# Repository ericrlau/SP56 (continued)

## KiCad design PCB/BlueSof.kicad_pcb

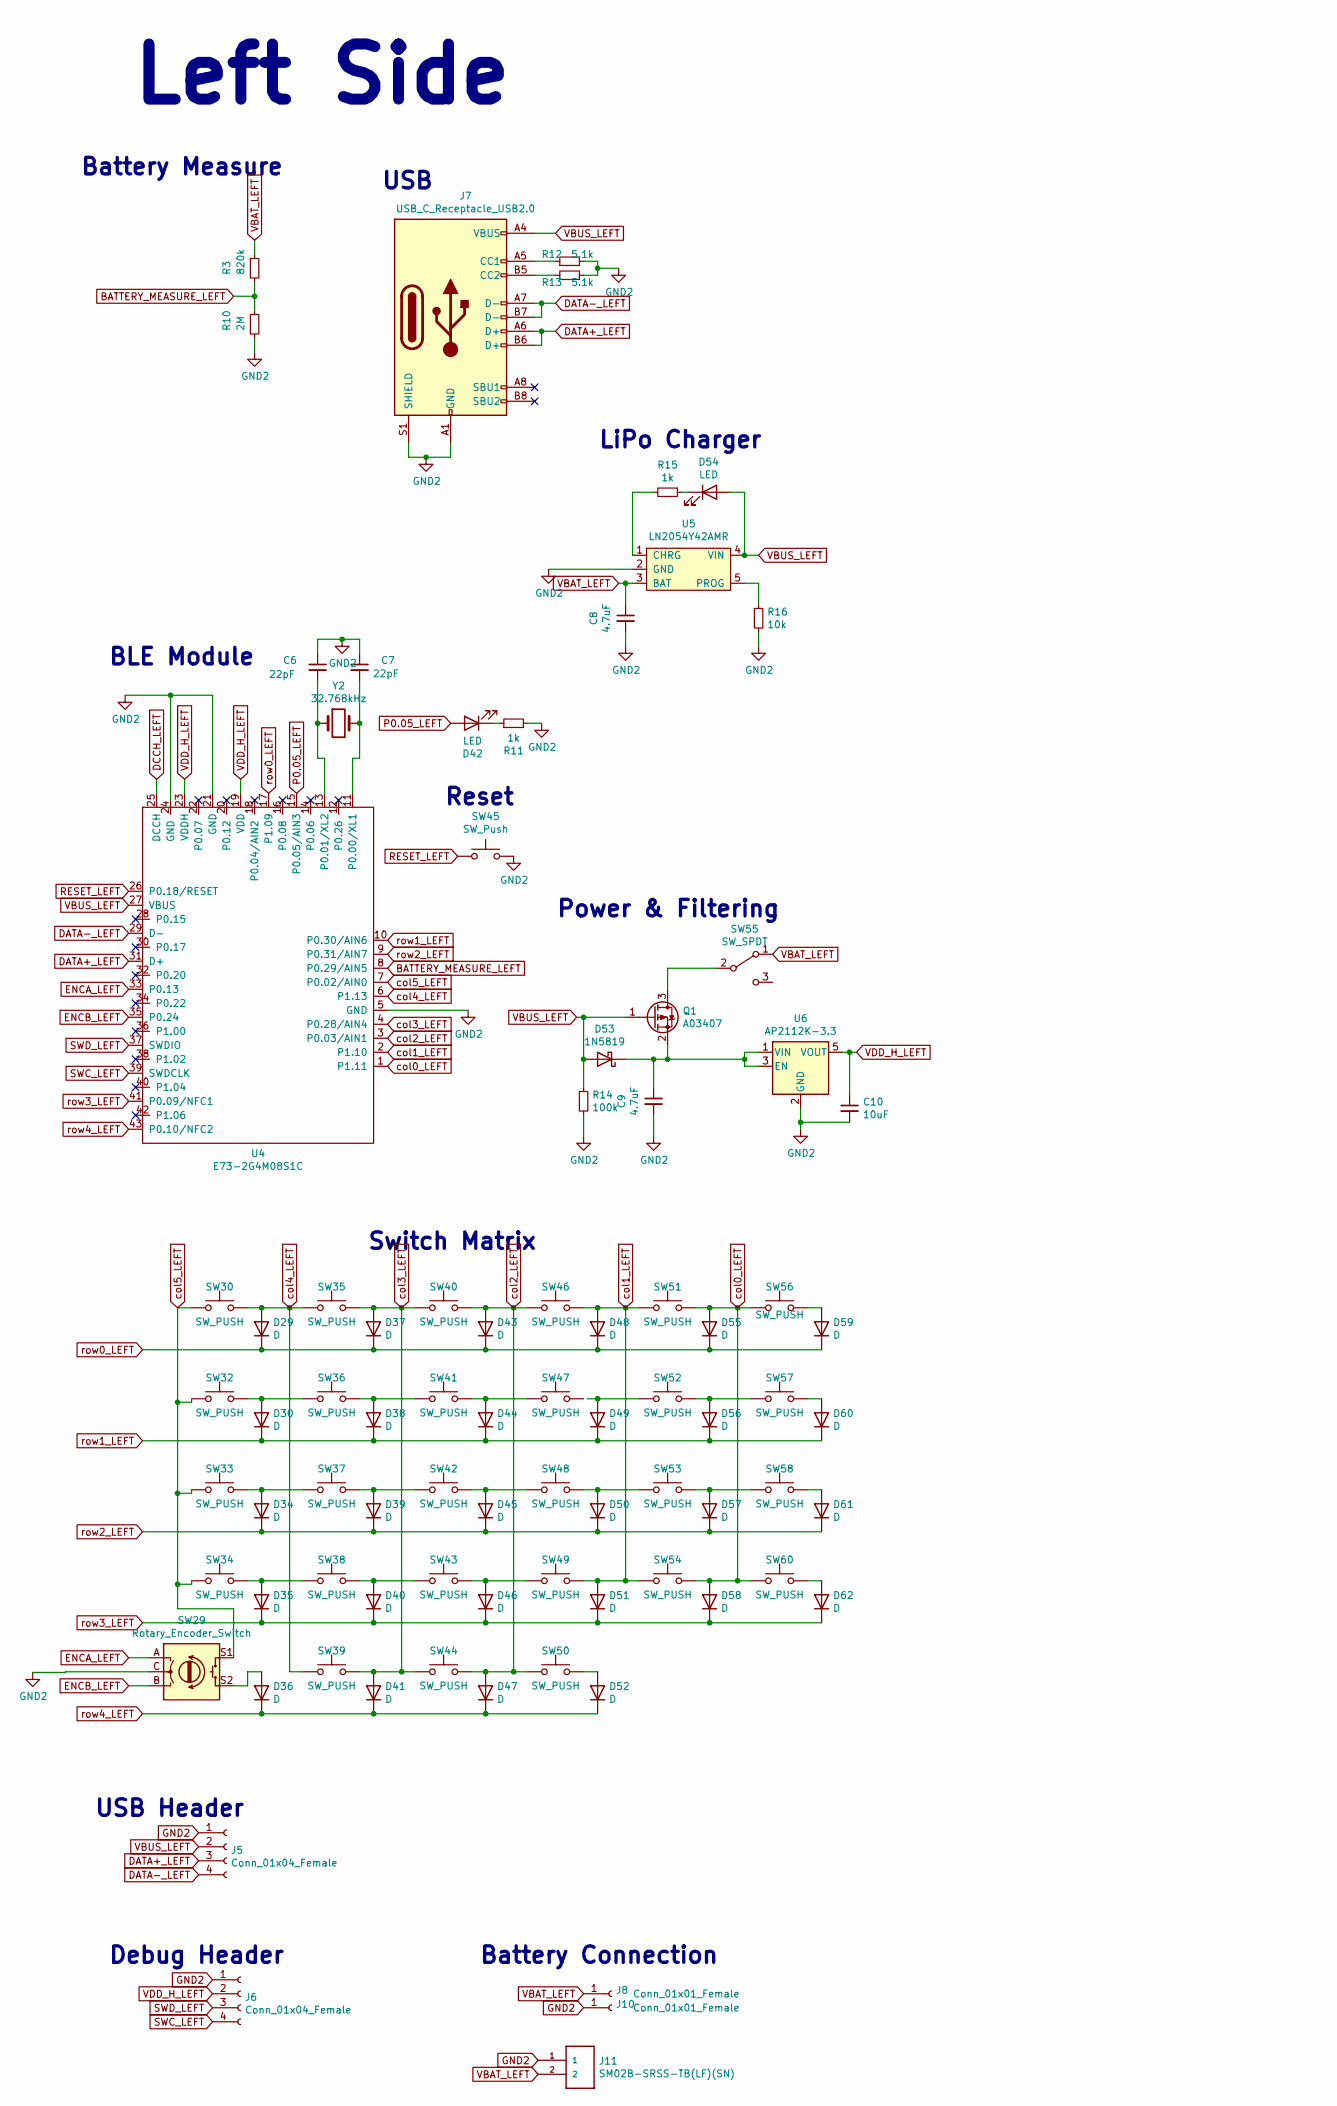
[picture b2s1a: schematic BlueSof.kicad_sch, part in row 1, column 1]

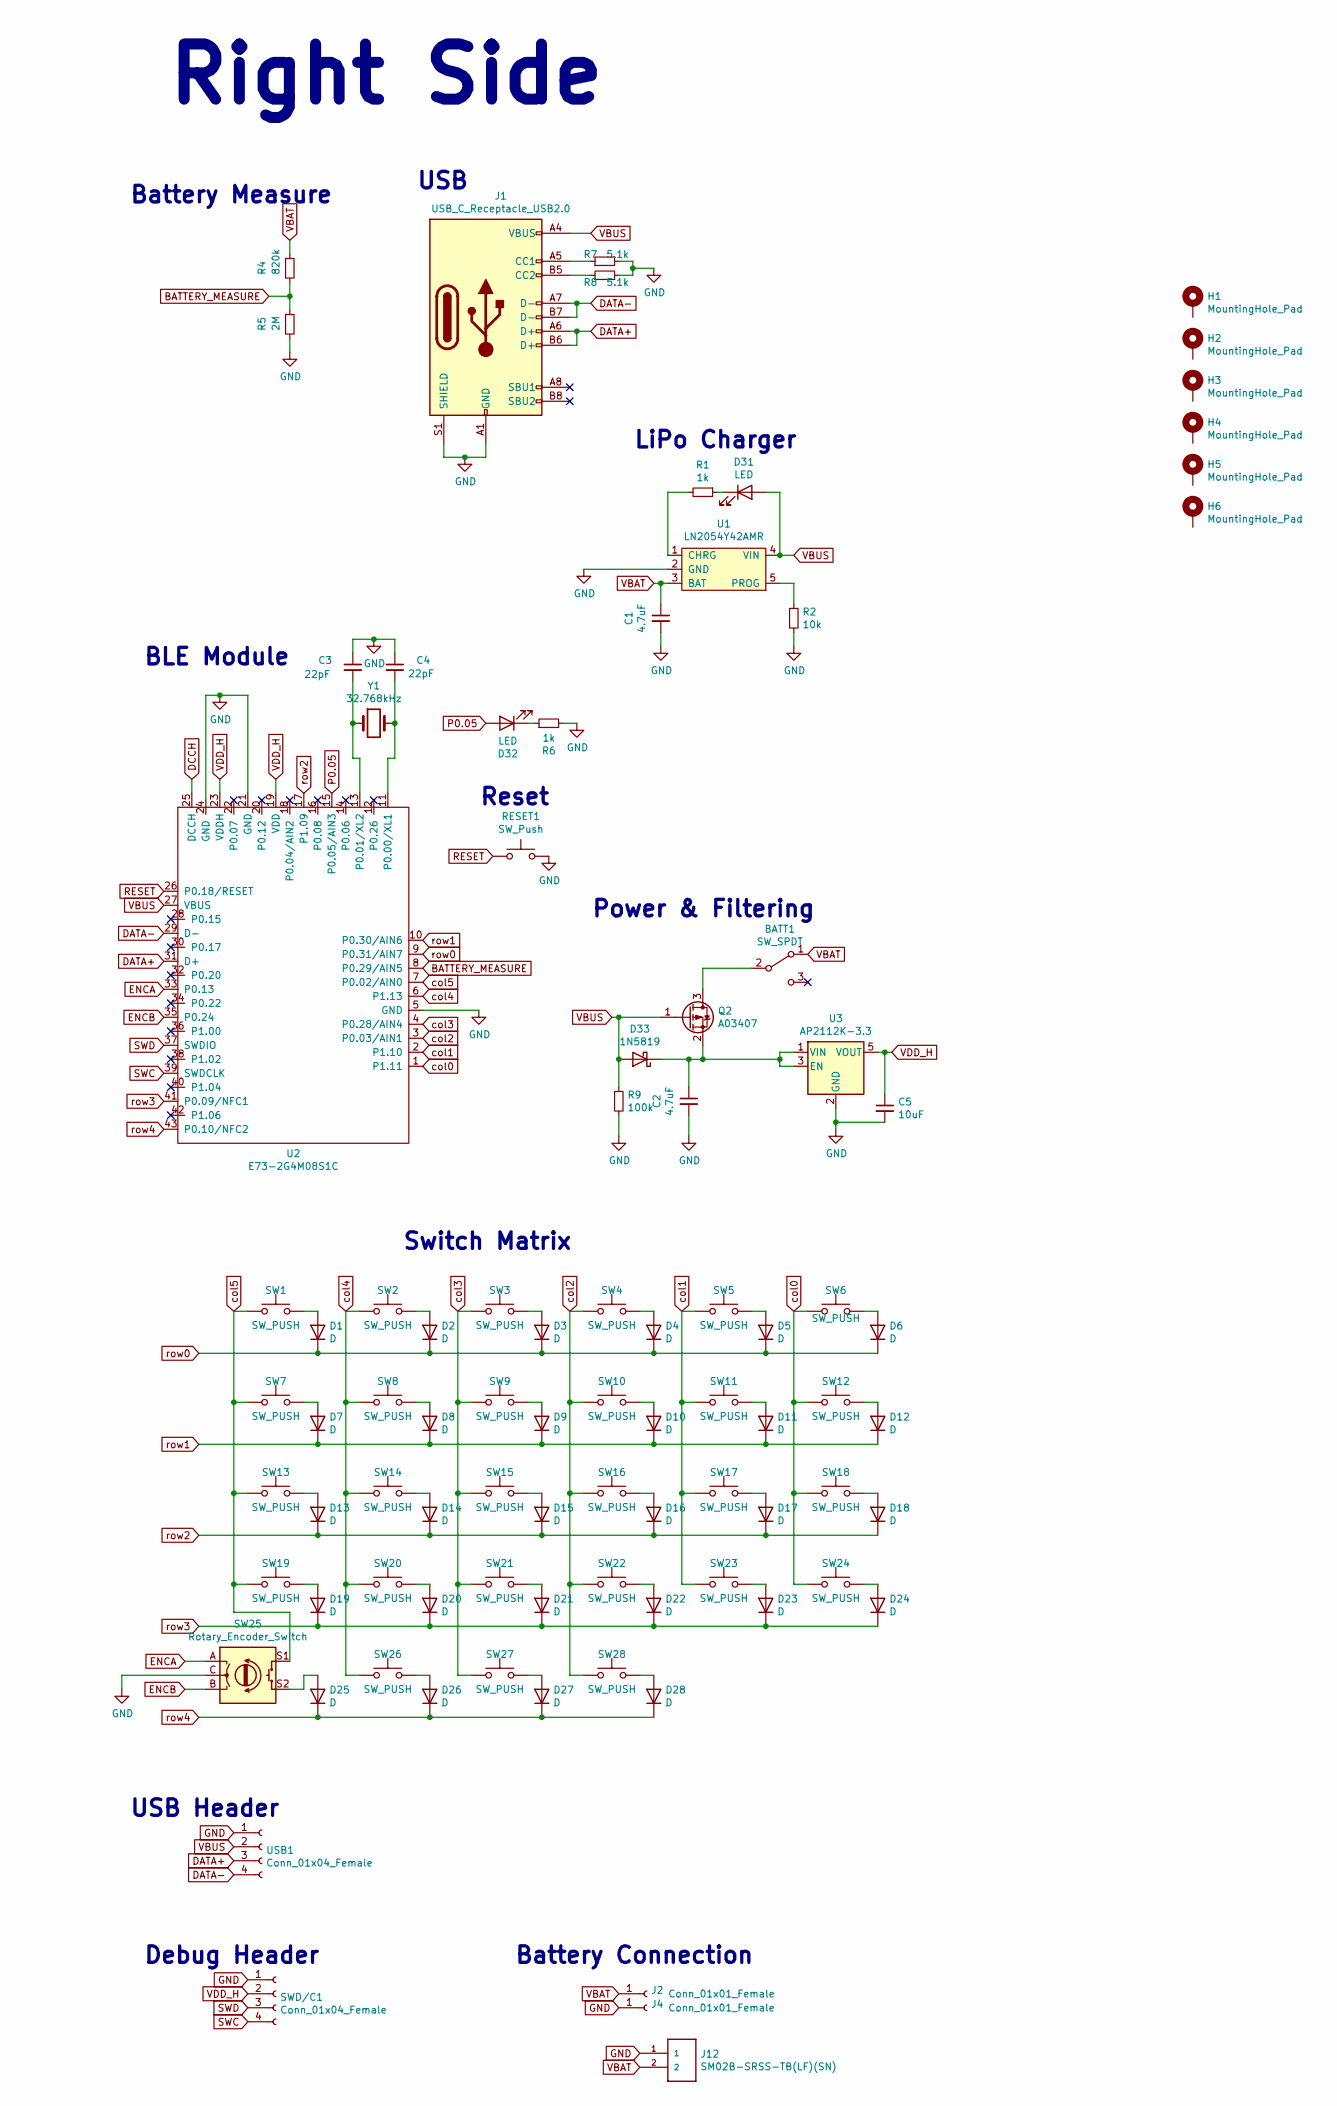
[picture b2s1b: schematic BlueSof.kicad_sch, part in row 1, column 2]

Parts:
BATT1: SW_SPDT; SW-TH_MSK12C02
C1, C2, C8, C9: 4.7uF; C_0603_1608Metric_Pad1.08x0.95mm_HandSolder
C3, C4, C6, C7: 22pF; C_0603_1608Metric_Pad1.08x0.95mm_HandSolder
C5, C10: 10uF; C_0603_1608Metric_Pad1.08x0.95mm_HandSolder
D1, D2, D3, D4, D5, D6, D7, D8, D9, D10, D11, D12, D13, D14, D15, D16, D17, D18, D19, D20, D21, D22, D23, D24, D25, D26, D27, D28, D29, D30, D34, D35, D36, D37, D38, D39, D40, D41, D43, D44, D45, D46, D47, D48, D49, D50, D51, D52, D55, D56, D57, D58, D59, D60, D61, D62: D; D_SOD-123
D31, D32, D42, D54: LED; LED_0603_1608Metric_Pad1.05x0.95mm_HandSolder
D33, D53: 1N5819; D_SOD-323_HandSoldering
H1, H2, H3, H4, H5, H6: MountingHole_Pad
J1, J7: USB_C_Receptacle_USB2.0; USB-C_C168688
J2, J4, J8, J10: Conn_01x01_Female; PinHeader_1x01_P2.54mm_Vertical
J5, J6: Conn_01x04_Female; PinHeader_1x04_P2.54mm_Vertical
J11, J12: SM02B-SRSS-TB(LF)(SN)
Q1, Q2: A03407; SOT-23
R1, R6, R11, R15: 1k; R_0603_1608Metric_Pad0.98x0.95mm_HandSolder
R2, R16: 10k; R_0603_1608Metric_Pad0.98x0.95mm_HandSolder
R3, R4: 820k; R_0603_1608Metric_Pad0.98x0.95mm_HandSolder
R5, R10: 2M; R_0603_1608Metric_Pad0.98x0.95mm_HandSolder
R7, R8, R12, R13: 5.1k; R_0603_1608Metric_Pad0.98x0.95mm_HandSolder
R9, R14: 100k; R_0603_1608Metric_Pad0.98x0.95mm_HandSolder
RESET1: SW_Push; SW_SPST_B3U-1000P
SW1, SW2, SW3, SW4, SW5, SW6, SW7, SW8, SW9, SW10, SW11, SW12, SW13, SW14, SW15, SW16, SW17, SW18, SW19, SW20, SW21, SW22, SW23, SW24, SW27, SW28, SW30, SW32, SW33, SW34, SW35, SW36, SW37, SW38, SW40, SW41, SW42, SW43, SW44, SW46, SW47, SW48, SW49, SW50, SW51, SW52, SW53, SW54, SW56, SW57, SW58, SW60: SW_PUSH; KailhLowProfile
SW25, SW29: Rotary_Encoder_Switch; RotaryEncoder_Alps_EC11E-Switch_Vertical_H20mm
SW26, SW39: SW_PUSH; KailhLowProfile_1.5U
SW45: SW_Push; SW_SPST_B3U-1000P
SW55: SW_SPDT; SW-TH_MSK12C02
SWD/C1: Conn_01x04_Female; PinHeader_1x04_P2.54mm_Vertical
U1, U5: LN2054Y42AMR; SOT-23-5
U2, U4: E73-2G4M08S1C; E73-2G4M08S1C-52840
U3, U6: AP2112K-3.3; SOT-23-5
USB1: Conn_01x04_Female; PinHeader_1x04_P2.54mm_Vertical
Y1, Y2: 32.768kHz; Crystal_SMD_MicroCrystal_CM9V-T1A-2Pin_1.6x1.0mm_HandSolder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

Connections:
BATTERY_MEASURE: R4.2, R5.1, U2.8 (P0.29/AIN5)
BATTERY_MEASURE_LEFT: R3.2, R10.1, U4.8 (P0.29/AIN5)
DATA+: J1.A6 (D+), J1.B6 (D+), U2.31 (D+), USB1.3
DATA+_LEFT: J5.3, J7.A6 (D+), J7.B6 (D+), U4.31 (D+)
DATA-: J1.A7 (D-), J1.B7 (D-), U2.29 (D-), USB1.4
DATA-_LEFT: J5.4, J7.A7 (D-), J7.B7 (D-), U4.29 (D-)
DCCH: U2.25 (DCCH)
DCCH_LEFT: U4.25 (DCCH)
ENCA: SW25.A, U2.33 (P0.13)
ENCA_LEFT: SW29.A, U4.33 (P0.13)
ENCB: SW25.B, U2.35 (P0.24)
ENCB_LEFT: SW29.B, U4.35 (P0.24)
GND: C1.2, C2.2, C3.1, C4.1, C5.2, J1.A1 (GND), J1.A12 (GND), J1.B1 (GND), J1.B12 (GND), J1.S1 (SHIELD), J4.1, J12.1, R2.2, R5.2, R6.2, R7.2, R8.2, R9.2, RESET1.2, SW25.C, SWD/C1.1, U1.2 (GND), U2.5 (GND), U2.21 (GND), U2.24 (GND), U3.2 (GND), USB1.1
unnamed: BATT1.2 (B), Q2.3 (D)
unnamed: C2.1, D33.1 (K), Q2.2 (S), U3.1 (VIN), U3.3 (EN)
unnamed: C3.2, U2.13 (P0.01/XL2), Y1.1
unnamed: C4.2, U2.11 (P0.00/XL1), Y1.2
unnamed: C6.2, U4.13 (P0.01/XL2), Y2.1
unnamed: C7.2, U4.11 (P0.00/XL1), Y2.2
unnamed: C9.1, D53.1 (K), Q1.2 (S), U6.1 (VIN), U6.3 (EN)
unnamed: D1.2 (A), SW1.2
unnamed: D2.2 (A), SW2.2
unnamed: D3.2 (A), SW3.2
unnamed: D4.2 (A), SW4.2
unnamed: D5.2 (A), SW5.2
unnamed: D6.2 (A), SW6.2
unnamed: D7.2 (A), SW7.2
unnamed: D8.2 (A), SW8.2
unnamed: D9.2 (A), SW9.2
unnamed: D10.2 (A), SW10.2
unnamed: D11.2 (A), SW11.2
unnamed: D12.2 (A), SW12.2
unnamed: D13.2 (A), SW13.2
unnamed: D14.2 (A), SW14.2
unnamed: D15.2 (A), SW15.2
unnamed: D16.2 (A), SW16.2
unnamed: D17.2 (A), SW17.2
unnamed: D18.2 (A), SW18.2
unnamed: D19.2 (A), SW19.2
unnamed: D20.2 (A), SW20.2
unnamed: D21.2 (A), SW21.2
unnamed: D22.2 (A), SW22.2
unnamed: D23.2 (A), SW23.2
unnamed: D24.2 (A), SW24.2
unnamed: D25.2 (A), SW25.S2
unnamed: D26.2 (A), SW26.2
unnamed: D27.2 (A), SW27.2
unnamed: D28.2 (A), SW28.2
unnamed: D30.2 (A), SW32.2, SW36.1
unnamed: D31.1 (K), R1.1
unnamed: D32.1 (K), R6.1
unnamed: D34.2 (A), SW33.2, SW37.1
unnamed: D35.2 (A), SW34.2, SW38.1
unnamed: D36.2 (A), SW29.S2
unnamed: D38.2 (A), SW36.2, SW41.1
unnamed: D39.2 (A), SW37.2, SW42.1
unnamed: D40.2 (A), SW38.2, SW43.1
unnamed: D42.1 (K), R11.1
unnamed: D44.2 (A), SW41.2, SW47.1
unnamed: D45.2 (A), SW42.2, SW48.1
unnamed: D46.2 (A), SW43.2, SW49.1
unnamed: D49.2 (A), SW52.1
unnamed: D50.2 (A), SW48.2, SW53.1
unnamed: D52.2 (A), SW50.2
unnamed: D54.1 (K), R15.1
unnamed: D56.2 (A), SW52.2, SW57.1
unnamed: D57.2 (A), SW53.2, SW58.1
unnamed: D59.2 (A), SW56.2
unnamed: D60.2 (A), SW57.2
unnamed: D61.2 (A), SW58.2
unnamed: D62.2 (A), SW60.2
unnamed: J1.A5 (CC1), R7.1
unnamed: J1.B5 (CC2), R8.1
unnamed: J7.A5 (CC1), R12.1
unnamed: J7.B5 (CC2), R13.1
unnamed: Q1.3 (D), SW55.2 (B)
unnamed: R1.2, U1.1 (CHRG)
unnamed: R2.1, U1.5 (PROG)
unnamed: R15.2, U5.1 (CHRG)
unnamed: R16.1, U5.5 (PROG)
P0.05: D32.2 (A), U2.15 (P0.05/AIN3)
P0.05_LEFT: D42.2 (A), U4.15 (P0.05/AIN3)
RESET: RESET1.1, U2.26 (P0.18/RESET)
RESET_LEFT: SW45.1, U4.26 (P0.18/RESET)
SWC: SWD/C1.4, U2.39 (SWDCLK)
SWC_LEFT: J6.4, U4.39 (SWDCLK)
SWD: SWD/C1.3, U2.37 (SWDIO)
SWD_LEFT: J6.3, U4.37 (SWDIO)
VBAT: BATT1.1 (A), C1.1, J2.1, J12.2, R4.1, U1.3 (BAT)
VBAT_LEFT: C8.1, J8.1, J11.2, R3.1, SW55.1 (A), U5.3 (BAT)
VBUS: D31.2 (A), D33.2 (A), J1.A4 (VBUS), J1.A9 (VBUS), J1.B4 (VBUS), J1.B9 (VBUS), Q2.1 (G), R9.1, U1.4 (VIN), U2.27 (VBUS), USB1.2
VBUS_LEFT: D53.2 (A), D54.2 (A), J5.2, J7.A4 (VBUS), J7.A9 (VBUS), J7.B4 (VBUS), J7.B9 (VBUS), Q1.1 (G), R14.1, U4.27 (VBUS), U5.4 (VIN)
VDD_H: C5.1, SWD/C1.2, U2.19 (VDD), U2.23 (VDDH), U3.5 (VOUT)
VDD_H_LEFT: C10.1, J6.2, U4.19 (VDD), U4.23 (VDDH), U6.5 (VOUT)
col0: SW6.1, SW12.1, SW18.1, SW24.1, U2.1 (P1.11)
col0_LEFT: D55.2 (A), D58.2 (A), SW51.2, SW54.2, SW56.1, SW60.1, U4.1 (P1.11)
col1: SW5.1, SW11.1, SW17.1, SW23.1, U2.2 (P1.10)
col1_LEFT: D48.2 (A), D51.2 (A), SW46.2, SW49.2, SW51.1, SW54.1, U4.2 (P1.10)
col2: SW4.1, SW10.1, SW16.1, SW22.1, SW28.1, U2.3 (P0.03/AIN1)
col2_LEFT: D43.2 (A), D47.2 (A), SW40.2, SW44.2, SW46.1, SW50.1, U4.3 (P0.03/AIN1)
col3: SW3.1, SW9.1, SW15.1, SW21.1, SW27.1, U2.4 (P0.28/AIN4)
col3_LEFT: D37.2 (A), D41.2 (A), SW35.2, SW39.2, SW40.1, SW44.1, U4.4 (P0.28/AIN4)
col4: SW2.1, SW8.1, SW14.1, SW20.1, SW26.1, U2.6 (P1.13)
col4_LEFT: D29.2 (A), SW30.2, SW35.1, SW39.1, U4.6 (P1.13)
col5: SW1.1, SW7.1, SW13.1, SW19.1, SW25.S1, U2.7 (P0.02/AIN0)
col5_LEFT: SW29.S1, SW30.1, SW32.1, SW33.1, SW34.1, U4.7 (P0.02/AIN0)
no_connect_126: BATT1.3 (C)
no_connect_127: J1.A8 (SBU1)
no_connect_128: J1.B8 (SBU2)
no_connect_129: J7.A8 (SBU1)
no_connect_130: J7.B8 (SBU2)
no_connect_131: U2.12 (P0.26)
no_connect_132: U2.14 (P0.06)
no_connect_133: U2.16 (P0.08)
no_connect_134: U2.18 (P0.04/AIN2)
no_connect_135: U2.20 (P0.12)
no_connect_136: U2.22 (P0.07)
no_connect_137: U2.28 (P0.15)
no_connect_138: U2.30 (P0.17)
no_connect_139: U2.32 (P0.20)
no_connect_140: U2.34 (P0.22)
no_connect_141: U2.36 (P1.00)
no_connect_142: U2.38 (P1.02)
no_connect_143: U2.40 (P1.04)
no_connect_144: U2.42 (P1.06)
no_connect_145: U3.4 (NC)
no_connect_146: U4.12 (P0.26)
no_connect_147: U4.14 (P0.06)
no_connect_148: U4.16 (P0.08)
no_connect_149: U4.18 (P0.04/AIN2)
no_connect_150: U4.20 (P0.12)
no_connect_151: U4.22 (P0.07)
no_connect_152: U4.28 (P0.15)
no_connect_153: U4.30 (P0.17)
no_connect_154: U4.32 (P0.20)
no_connect_155: U4.34 (P0.22)
no_connect_156: U4.36 (P1.00)
no_connect_157: U4.38 (P1.02)
no_connect_158: U4.40 (P1.04)
no_connect_159: U4.42 (P1.06)
no_connect_160: U6.4 (NC)
row0: D1.1 (K), D2.1 (K), D3.1 (K), D4.1 (K), D5.1 (K), D6.1 (K), U2.9 (P0.31/AIN7)
row0_LEFT: D29.1 (K), D37.1 (K), D43.1 (K), D48.1 (K), D55.1 (K), D59.1 (K), U4.17 (P1.09)
row1: D7.1 (K), D8.1 (K), D9.1 (K), D10.1 (K), D11.1 (K), D12.1 (K), U2.10 (P0.30/AIN6)
row1_LEFT: D30.1 (K), D38.1 (K), D44.1 (K), D49.1 (K), D56.1 (K), D60.1 (K), U4.10 (P0.30/AIN6)
row2: D13.1 (K), D14.1 (K), D15.1 (K), D16.1 (K), D17.1 (K), D18.1 (K), U2.17 (P1.09)
row2_LEFT: D34.1 (K), D39.1 (K), D45.1 (K), D50.1 (K), D57.1 (K), D61.1 (K), U4.9 (P0.31/AIN7)
row3: D19.1 (K), D20.1 (K), D21.1 (K), D22.1 (K), D23.1 (K), D24.1 (K), U2.41 (P0.09/NFC1)
row3_LEFT: D35.1 (K), D40.1 (K), D46.1 (K), D51.1 (K), D58.1 (K), D62.1 (K), U4.41 (P0.09/NFC1)
row4: D25.1 (K), D26.1 (K), D27.1 (K), D28.1 (K), U2.43 (P0.10/NFC2)
row4_LEFT: D36.1 (K), D41.1 (K), D47.1 (K), D52.1 (K), U4.43 (P0.10/NFC2)

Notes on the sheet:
Battery Measure
USB Header
BLE Module
Debug Header
Left Side
Switch Matrix
USB
Reset
Battery Connection
Power & Filtering
LiPo Charger
Right Side

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
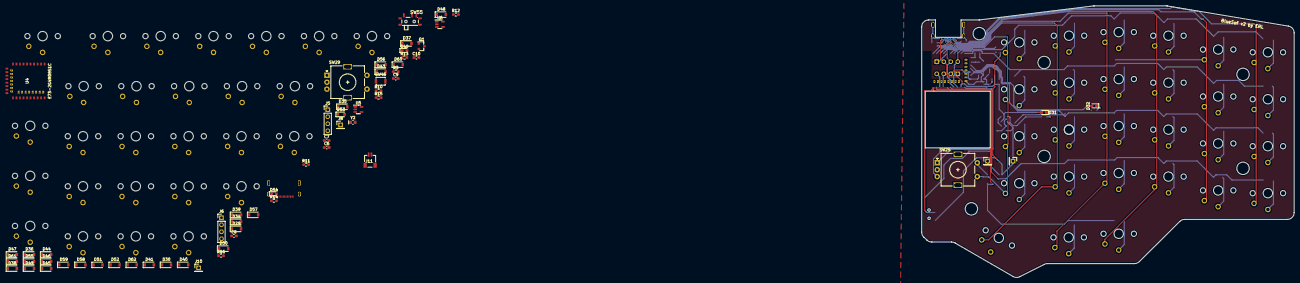
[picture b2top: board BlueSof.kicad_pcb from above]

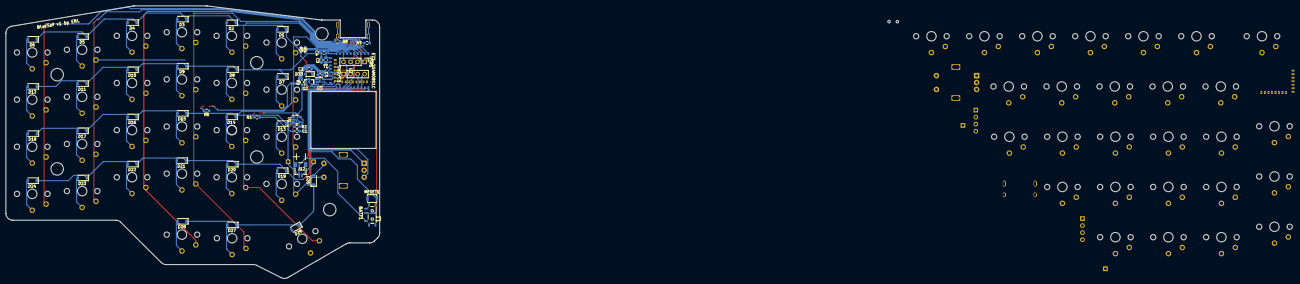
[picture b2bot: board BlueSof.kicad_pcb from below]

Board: 2 copper layers, 134.8 x 98.3 mm, 176 parts (53 on the bottom side), 115 nets.

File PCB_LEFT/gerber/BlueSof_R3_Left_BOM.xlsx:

Id | Designator | Description | Quantity | Value | Package | LCSC PN | NOTE
1.0 | SW1,SW2,SW4,SW5,SW6,SW7,SW8,SW9,SW10,SW12,SW14,SW15,SW16,SW17,SW19,SW21,SW22,SW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 | KailhLowProfile | 26.0 | SW_PUSH | 0603 | DNI | DNI
2.0 | SWD/C1 | PinHeader_1x04_P2.54mm_Vertical | 1.0 | Conn_01x04_Female | DNI | DNI | DNI
3.0 | D32,D31 | LED_0603_1608Metric_Pad1.05x0.95mm_HandSolder | 2.0 | LED | DNI | DNI | DNI
4.0 | SW26 | KailhLowProfile_1.5U | 1.0 | SW_PUSH | DNI | DNI | DNI
5.0 | SW25 | RotaryEncoder_Alps_EC11E-Switch_Vertical_H20mm | 1.0 | Rotary_Encoder_Switch | DNI | DNI | DNI
6.0 | D2,D3,D4,D5,D6,D7,D8,D9,D10,D11,D12,D14,D15,D16,D17,D18,D19,D20,D21,D22,D23,D24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 | D_SOD-123 | 28.0 | D | 0603 | C402213
7.0 | C5 | C_0603_1608Metric_Pad1.08x0.95mm_HandSolder | 1.0 | 10uF | 0603 | C326057
8.0 | C4,C3 | C_0603_1608Metric_Pad1.08x0.95mm_HandSolder | 2.0 | 22pF | 0603 | C1653
9.0 | C1,C2 | C_0603_1608Metric_Pad1.08x0.95mm_HandSolder | 2.0 | 4.7uF | 0603 | C19666
10.0 | J1 | USB-C_C168688 | 1.0 | USB_C_Receptacle_USB2.0 |  | C168688
11.0 | Q2 | SOT-23 | 1.0 | A03407 | SOT-23 | C351408
12.0 | R2 | R_0603_1608Metric_Pad0.98x0.95mm_HandSolder | 1.0 | 10k | 0603 | C98220
13.0 | R4 | R_0603_1608Metric_Pad0.98x0.95mm_HandSolder | 1.0 | 820k | 0603 | C23252
14.0 | R5 | R_0603_1608Metric_Pad0.98x0.95mm_HandSolder | 1.0 | 2M | 0603 | C177282
15.0 | R7,R8 | R_0603_1608Metric_Pad0.98x0.95mm_HandSolder | 2.0 | 5.1k | 0603 | C105580
16.0 | R9 | R_0603_1608Metric_Pad0.98x0.95mm_HandSolder | 1.0 | 100k | 0603 | C14675
17.0 | RESET | SW_SPST_B3U-1000P | 1.0 | SW_Push |  | C231329
18.0 | U1 | SOT-23-5 | 1.0 | LN2054Y42AMR | SOT-23-5 | C141406
19.0 | U3 | SOT-23-5 | 1.0 | AP2112K-3.3 | SOT-23-5 | C51118
20.0 | Y1 | Crystal_SMD_MicroCrystal_CM9V-T1A-2Pin_1.6x1.0mm_HandSoldering | 1.0 | 32.768kHz | 1.6x1.0 | C93230
21.0 | R6,R1 | R_0603_1608Metric_Pad0.98x0.95mm_HandSolder | 2.0 | 1k | 0603 | C22548
22.0 | U2 | E73-2G4M08S1C-52840_minimal_inside_pads | 1.0 | E73-2G4M08S1C |  | C356849
23.0 | D33 | D_SOD-323_HandSoldering | 1.0 | 1N5819 | SOD-123 | C489147
24.0 | H6,H4,H5,H1,H2,H3 | MountingHole_4.3mm_M4 | 6.0 | MountingHole_Pad | DNI | DNI | DNI
25.0 | J12 | SM02B-SRSS-TB(LF)(SN) | 1.0 | SM02B-SRSS-TB_LF__SN_ |  | C160402
26.0 | BATT_SW | SW-TH_MSK12C02 | 1.0 | SW_SPDT |  | C431540

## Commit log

2020-12-06 initial
2020-12-08 initial layout
2020-12-09 before 2nd side
2020-12-09 EOD, layout on side 2 done, not routed
2020-12-09 autoroute done, still needs cleanup
2020-12-10 making progress on autoroute cleanup
2020-12-13 ordered first boards
2020-12-14 R2 version with minor fixes
2020-12-28 update switch footprint to reduce center hole size
2021-01-07 update to kicad6
2021-01-07 first commit, side 1
2021-01-09 getting close to layout on side 1
2021-01-20 initial route done, side 1
2021-01-23 right side draft done
2021-01-25 ordered left side from jlc
2021-02-22 minor updates for SMD assembly
2021-02-23 working towards next order
2021-02-26 layout almost done
2021-02-27 ready for jlc quote
2021-03-07 order SP56 R1 from JLC
2021-03-07 update license file
2021-03-20 clean up old files
2021-03-20 readme updates and minor cleanup
2021-03-21 cleanup and readme
2021-04-01 update readme and add build guide
2021-04-01 typo
